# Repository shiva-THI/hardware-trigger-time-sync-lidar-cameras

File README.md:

# hardware-trigger-time-sync-lidar-cameras
This repository contains the schematic design and PCB designs for two hardware-trigger circuits, designed using open-source software KiCAD. It also contains the arduino code used to obtain required time-delays.

Two folders are available:
1. lidar_and_three_cameras  (This contains design and code files for lidar with three camera - tested for roadside multi-sensor setup)
   -- kicad_files
   -- arduino_nano_files
2. lidar_and_seven_cameras (This contains design and code files for lidar with seven camera - designed for multi-sensor car)
   -- kicad_files
   -- arduino_nano_files

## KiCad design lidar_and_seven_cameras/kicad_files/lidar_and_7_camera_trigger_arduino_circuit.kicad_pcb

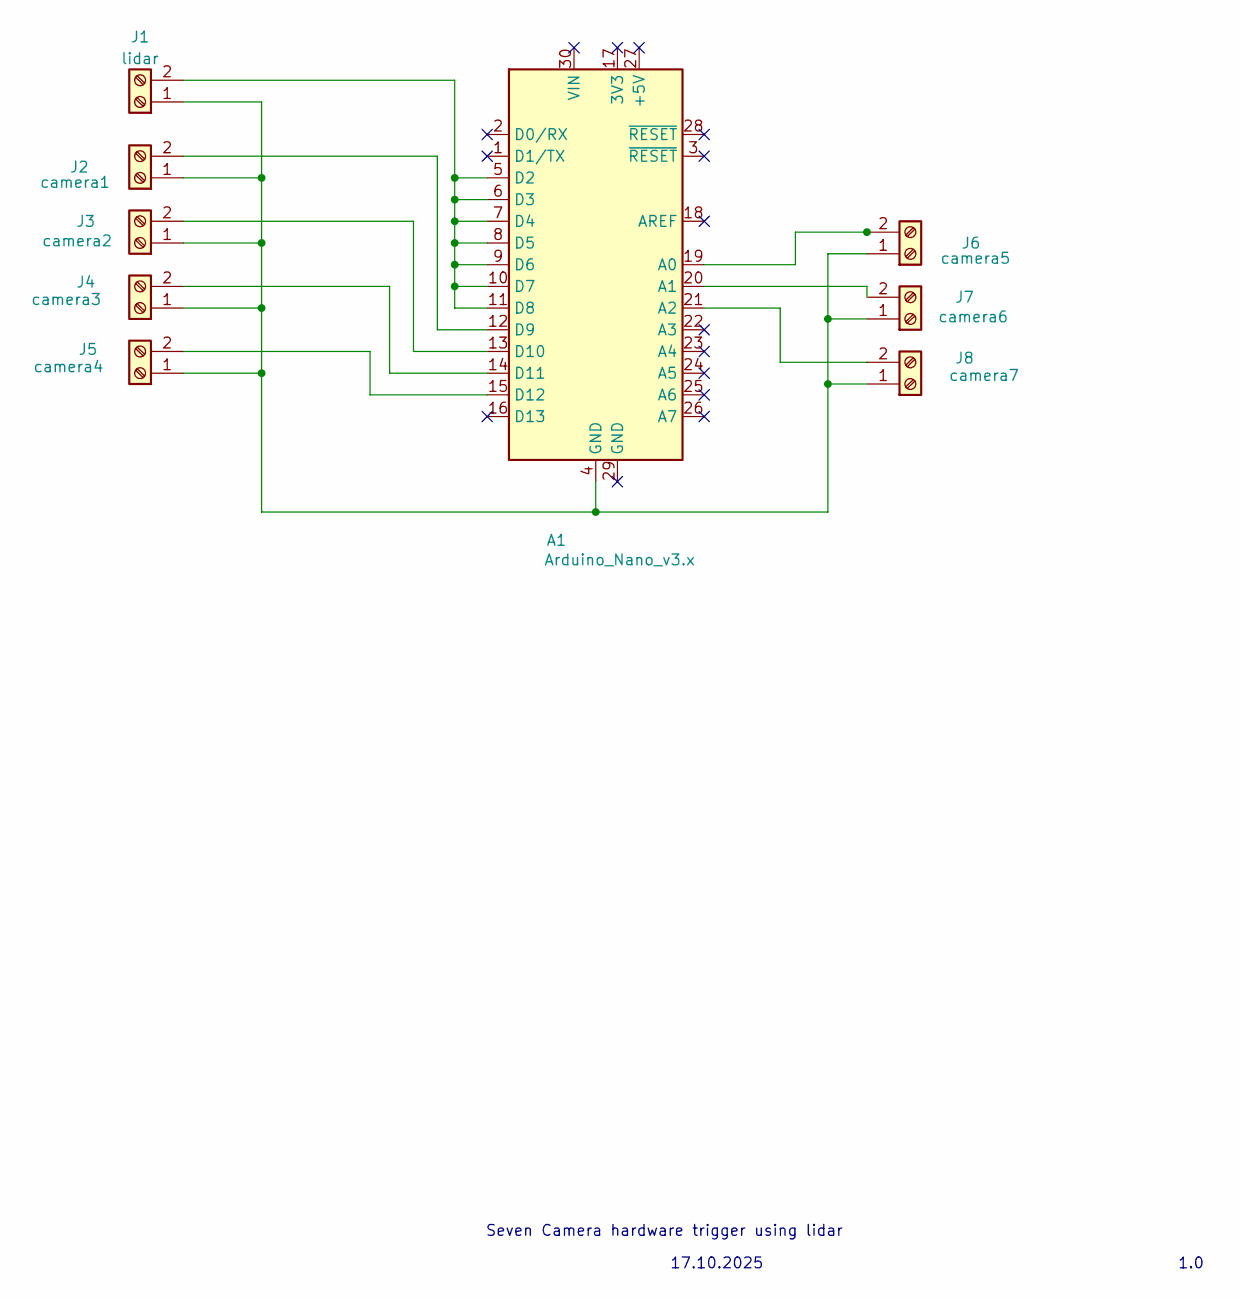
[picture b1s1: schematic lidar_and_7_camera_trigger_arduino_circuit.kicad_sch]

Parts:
A1: Arduino_Nano_v3.x; Arduino_Nano_WithMountingHoles
J1: lidar; TerminalBlock_Phoenix_MKDS-1,5-2_1x02_P5.00mm_Horizontal
J2: camera1; TerminalBlock_Phoenix_MKDS-1,5-2_1x02_P5.00mm_Horizontal
J3: camera2; TerminalBlock_Phoenix_MKDS-1,5-2_1x02_P5.00mm_Horizontal
J4: camera3; TerminalBlock_Phoenix_MKDS-1,5-2_1x02_P5.00mm_Horizontal
J5: camera4; TerminalBlock_Phoenix_MKDS-1,5-2_1x02_P5.00mm_Horizontal
J6: camera5; TerminalBlock_Phoenix_MKDS-1,5-2_1x02_P5.00mm_Horizontal
J7: camera6; TerminalBlock_Phoenix_MKDS-1,5-2_1x02_P5.00mm_Horizontal
J8: camera7; TerminalBlock_Phoenix_MKDS-1,5-2_1x02_P5.00mm_Horizontal

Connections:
unnamed: A1.19 (A0), J6.2
unnamed: A1.20 (A1), J7.2
unnamed: A1.21 (A2), J8.2
unnamed: A1.5 (D2), A1.6 (D3), A1.7 (D4), A1.8 (D5), A1.9 (D6), A1.10 (D7), A1.11 (D8), J1.2
unnamed: A1.12 (D9), J2.2
unnamed: A1.13 (D10), J3.2
unnamed: A1.14 (D11), J4.2
unnamed: A1.15 (D12), J5.2
unnamed: A1.4 (GND), J1.1, J2.1, J3.1, J4.1, J5.1, J6.1, J7.1, J8.1

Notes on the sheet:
Seven Camera hardware trigger using lidar
17.10.2025
1.0

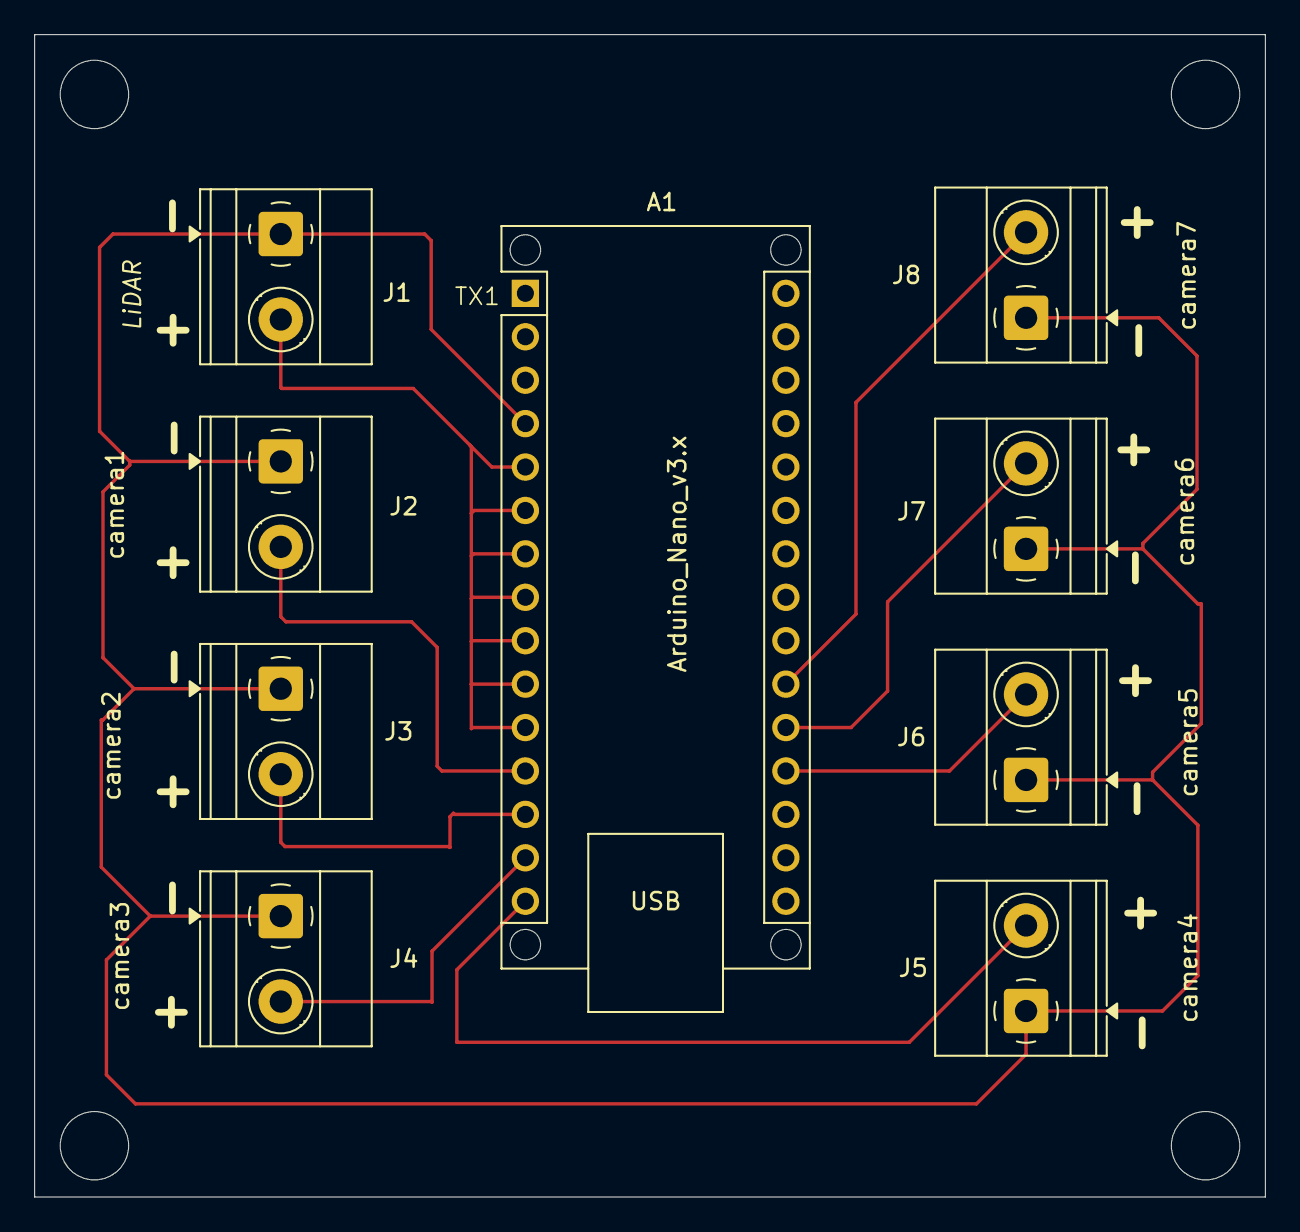
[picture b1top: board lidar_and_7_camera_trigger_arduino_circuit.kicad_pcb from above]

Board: 2 copper layers, 72.0 x 68.0 mm, 9 parts (0 on the bottom side), 9 nets.

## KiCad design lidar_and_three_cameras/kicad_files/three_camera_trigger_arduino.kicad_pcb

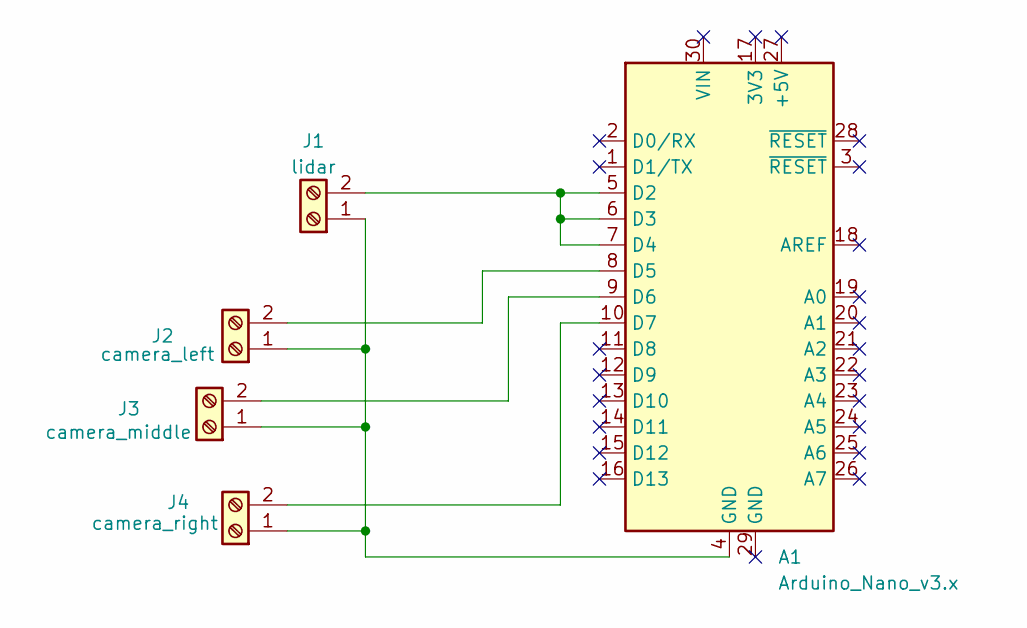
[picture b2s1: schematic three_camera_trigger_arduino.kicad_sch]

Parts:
A1: Arduino_Nano_v3.x; Arduino_Nano_WithMountingHoles
J1: lidar; TerminalBlock_Phoenix_MKDS-1,5-2_1x02_P5.00mm_Horizontal
J2: camera_left; TerminalBlock_Phoenix_MKDS-1,5-2_1x02_P5.00mm_Horizontal
J3: camera_middle; TerminalBlock_Phoenix_MKDS-1,5-2_1x02_P5.00mm_Horizontal
J4: camera_right; TerminalBlock_Phoenix_MKDS-1,5-2_1x02_P5.00mm_Horizontal

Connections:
unnamed: A1.5 (D2), A1.6 (D3), A1.7 (D4), J1.2
unnamed: A1.8 (D5), J2.2
unnamed: A1.9 (D6), J3.2
unnamed: A1.10 (D7), J4.2
unnamed: A1.4 (GND), J1.1, J2.1, J3.1, J4.1

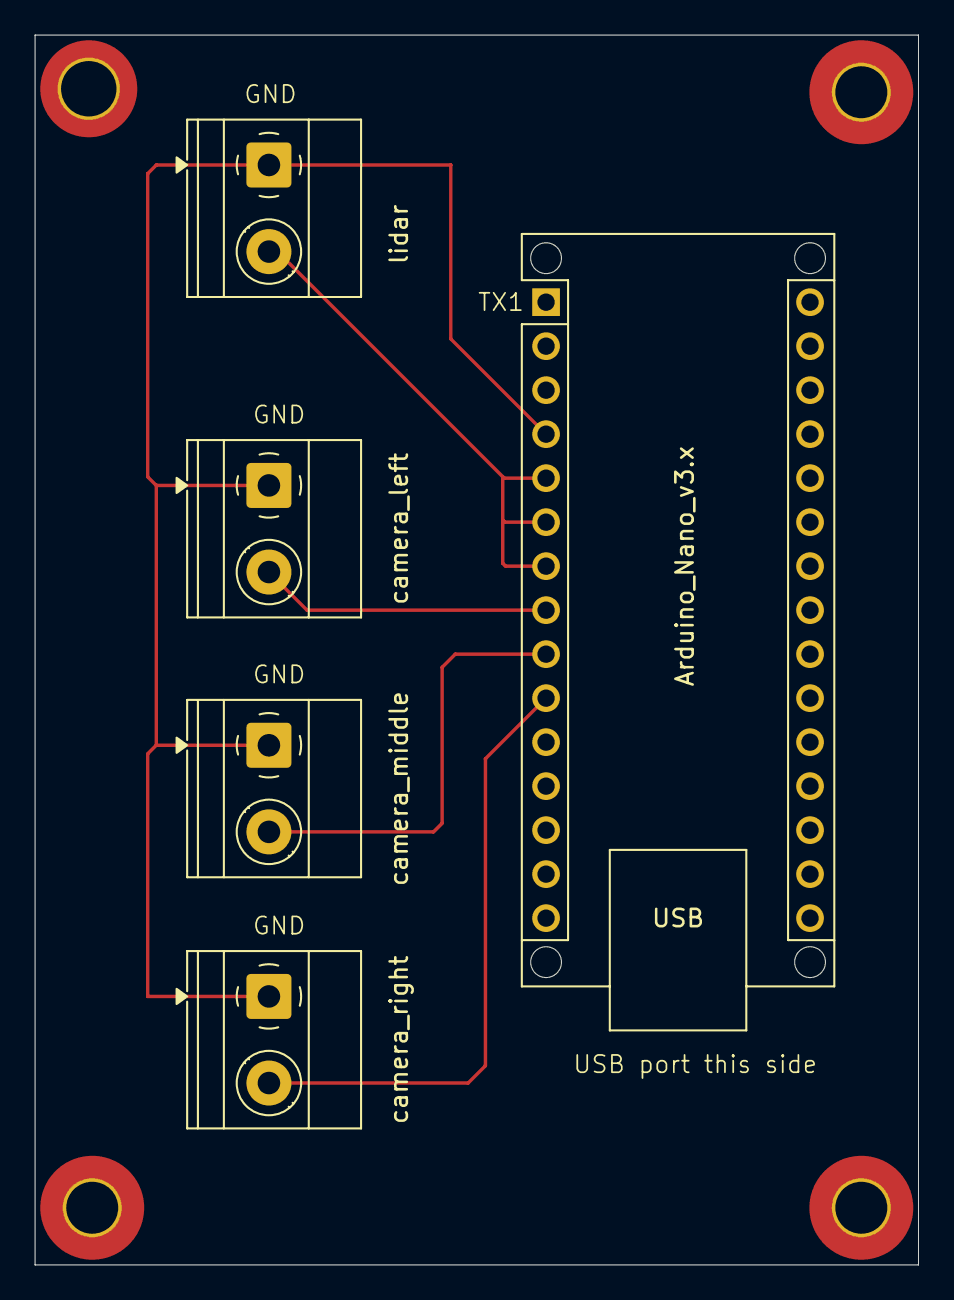
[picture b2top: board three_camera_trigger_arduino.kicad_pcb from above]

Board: 2 copper layers, 51.0 x 71.0 mm, 5 parts (0 on the bottom side), 5 nets.

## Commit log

2026-02-22 schematic, pcb design, and arduino nano code files are added
2026-02-22 Update README.md
    details of content added
